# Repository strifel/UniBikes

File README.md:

# UniBikes
Inspired by [traintrackr](https://www.traintrackr.io/) I wanted to create something similar for visualizing bikesharing bikes as my first ever PCB design.

Unibikes shows the 10 bike sharing locations at TU Dortmund University in germany with an RGB LED each.
Each LED can therefore represent if there are none, some or a few bikes at that station.

## Data
The micropython code directly receives the rgb values for each LED from a backend.

## Components
| Component name | Component        |
| -------------- | ---------------- |
| D1 to D10      | WS2812B LED      |
| J0             | USB C Receptable |
| J1 and J2      | 4 Pin header     |
| J3             | 2 Pin header     |
| U1             | ESP32 C3         |
| U2             | TLV1117 3.3V     |
| SW1 to SW3     | Push button      |
| R1             | 1k Resistor      |
| R2 to R4       | 10k Resistor     |
| R5 and R6      | 5.1k Resistor    |
| C1 and C4      | 10uF Capacitor   |
| C2             | 1 uF Capacitor   |
| C3             | 100nF Capacitor  |

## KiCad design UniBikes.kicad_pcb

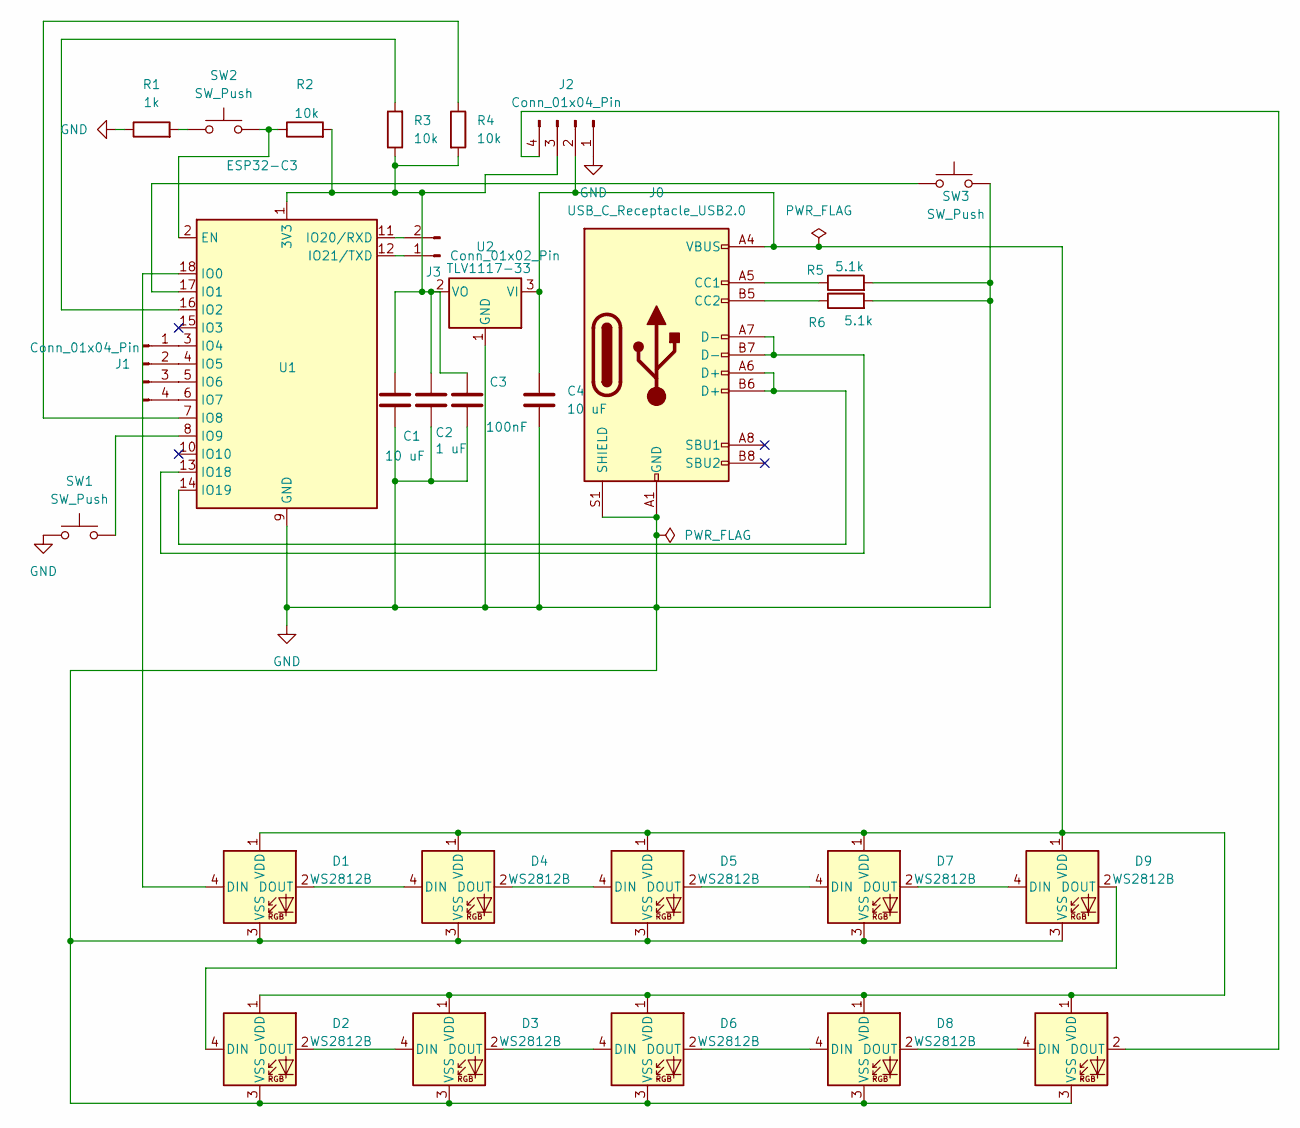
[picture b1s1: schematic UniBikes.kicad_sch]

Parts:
C1, C4: 10 uF; C_0603_1608Metric_Pad1.08x0.95mm_HandSolder
C2: 1 uF; C_0603_1608Metric_Pad1.08x0.95mm_HandSolder
C3: 100nF; C_0603_1608Metric_Pad1.08x0.95mm_HandSolder
D1, D2, D3, D4, D5, D6, D7, D8, D9, D10: WS2812B; LED_WS2812B_PLCC4_5.0x5.0mm_P3.2mm
J0: USB_C_Receptacle_USB2.0; USB_C_Receptacle_GCT_USB4110
J1, J2: Conn_01x04_Pin; PinSocket_1x04_P2.54mm_Vertical_SMD_Pin1Left
J3: Conn_01x02_Pin; PinSocket_1x02_P2.54mm_Vertical_SMD_Pin1Left
R1: 1k; R_0603_1608Metric_Pad0.98x0.95mm_HandSolder
R2, R3, R4: 10k; R_0603_1608Metric_Pad0.98x0.95mm_HandSolder
R5, R6: 5.1k; R_0603_1608Metric_Pad0.98x0.95mm_HandSolder
SW1, SW2, SW3: SW_Push; SW_Push_SPST_NO_Alps_SKRK
U1: ESP32-C3; ESP32-C3-WROOM-02
U2: TLV1117-33; SOT-223-3_TabPin2

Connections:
GND: C1.2, C2.2, C3.2, C4.2, D1.3 (VSS), D2.3 (VSS), D3.3 (VSS), D4.3 (VSS), D5.3 (VSS), D6.3 (VSS), D7.3 (VSS), D8.3 (VSS), D9.3 (VSS), D10.3 (VSS), J0.A1 (GND), J0.A12 (GND), J0.B1 (GND), J0.B12 (GND), J0.S1 (SHIELD), J2.1, R1.1, R5.2, R6.2, SW1.1, SW3.2, U1.9 (GND), U1.19 (GND), U2.1 (GND)
unnamed: D1.4 (DIN), U1.18 (IO0)
unnamed: D1.2 (DOUT), D4.4 (DIN)
unnamed: C4.1, D1.1 (VDD), D2.1 (VDD), D3.1 (VDD), D4.1 (VDD), D5.1 (VDD), D6.1 (VDD), D7.1 (VDD), D8.1 (VDD), D9.1 (VDD), D10.1 (VDD), J0.A4 (VBUS), J0.A9 (VBUS), J0.B4 (VBUS), J0.B9 (VBUS), J2.2, U2.3 (VI)
unnamed: D2.4 (DIN), D9.2 (DOUT)
unnamed: D2.2 (DOUT), D3.4 (DIN)
unnamed: D3.2 (DOUT), D6.4 (DIN)
unnamed: D4.2 (DOUT), D5.4 (DIN)
unnamed: D5.2 (DOUT), D7.4 (DIN)
unnamed: D6.2 (DOUT), D8.4 (DIN)
unnamed: D7.2 (DOUT), D9.4 (DIN)
unnamed: D8.2 (DOUT), D10.4 (DIN)
unnamed: D10.2 (DOUT), J2.4
unnamed: J0.A5 (CC1), R5.1
unnamed: J0.B5 (CC2), R6.1
unnamed: J1.1, U1.3 (IO4)
unnamed: J1.2, U1.4 (IO5)
unnamed: J1.3, U1.5 (IO6)
unnamed: J1.4, U1.6 (IO7)
unnamed: C1.1, C2.1, C3.1, J2.3, R2.2, R3.1, R4.2, U1.1 (3V3), U2.2 (VO)
unnamed: J3.1, U1.12 (IO21/TXD)
unnamed: J3.2, U1.11 (IO20/RXD)
unnamed: R1.2, SW2.1
unnamed: R2.1, SW2.2, U1.2 (EN)
unnamed: SW3.1, U1.17 (IO1)
unnamed: R3.2, U1.16 (IO2)
unnamed: R4.1, U1.7 (IO8)
unnamed: SW1.2, U1.8 (IO9)
unnamed: J0.A7 (D-), J0.B7 (D-), U1.13 (IO18)
unnamed: J0.A6 (D+), J0.B6 (D+), U1.14 (IO19)

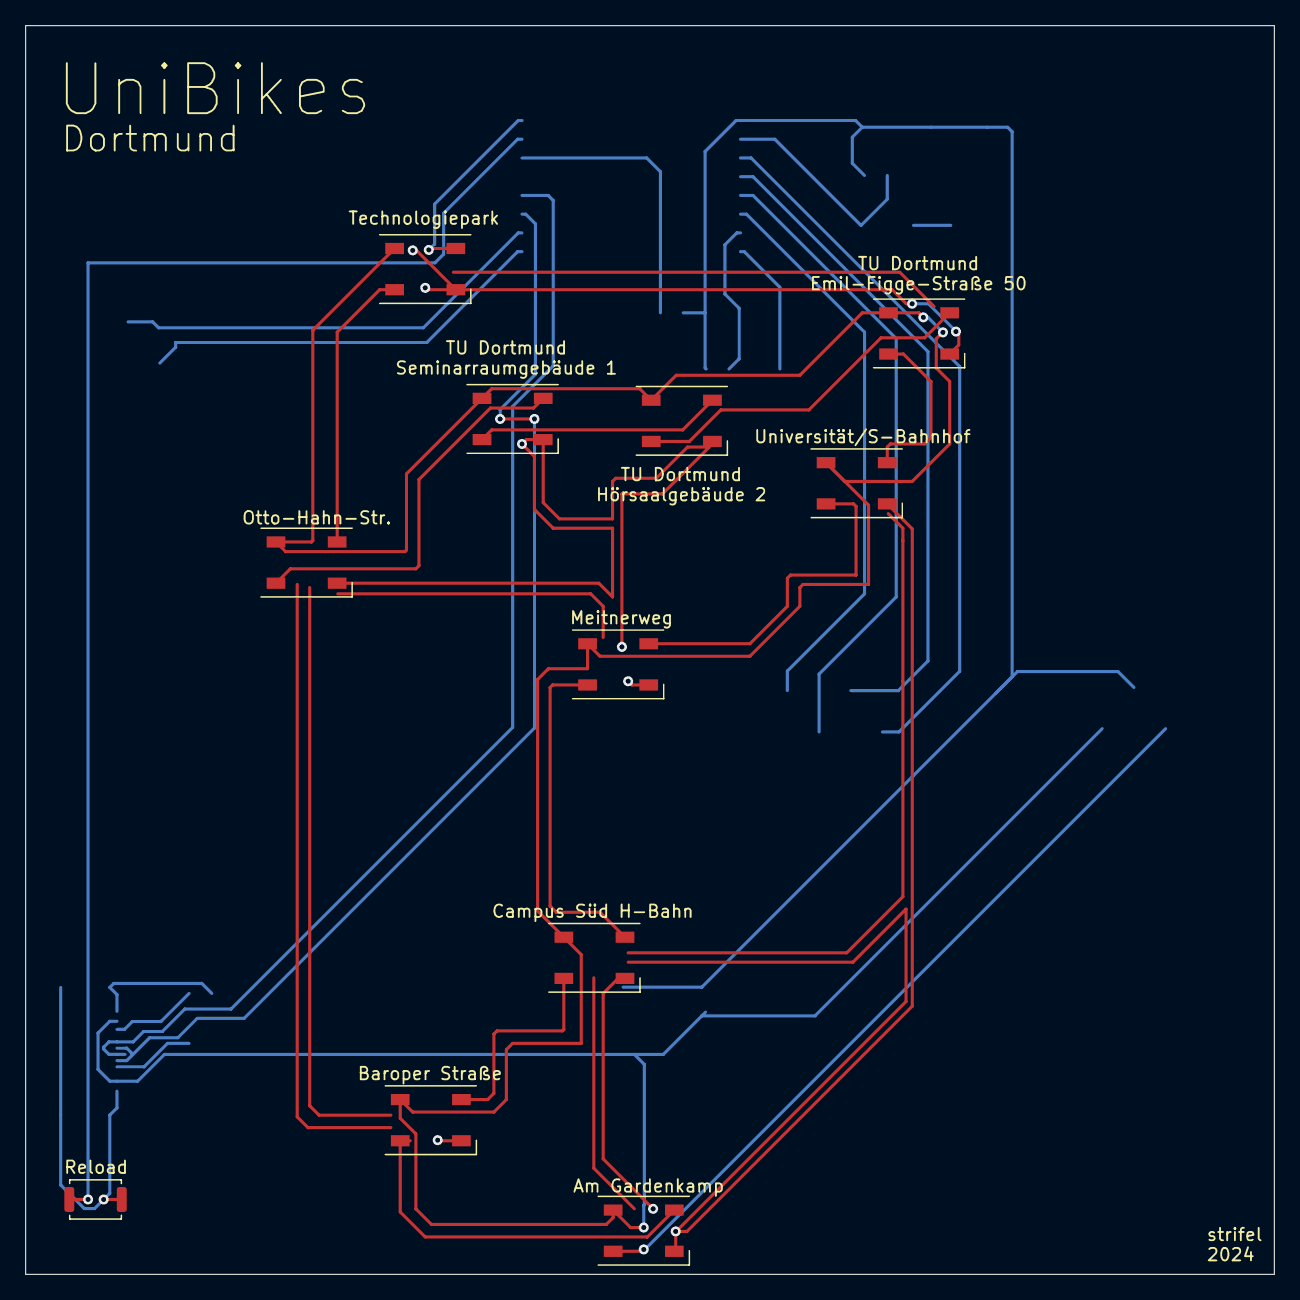
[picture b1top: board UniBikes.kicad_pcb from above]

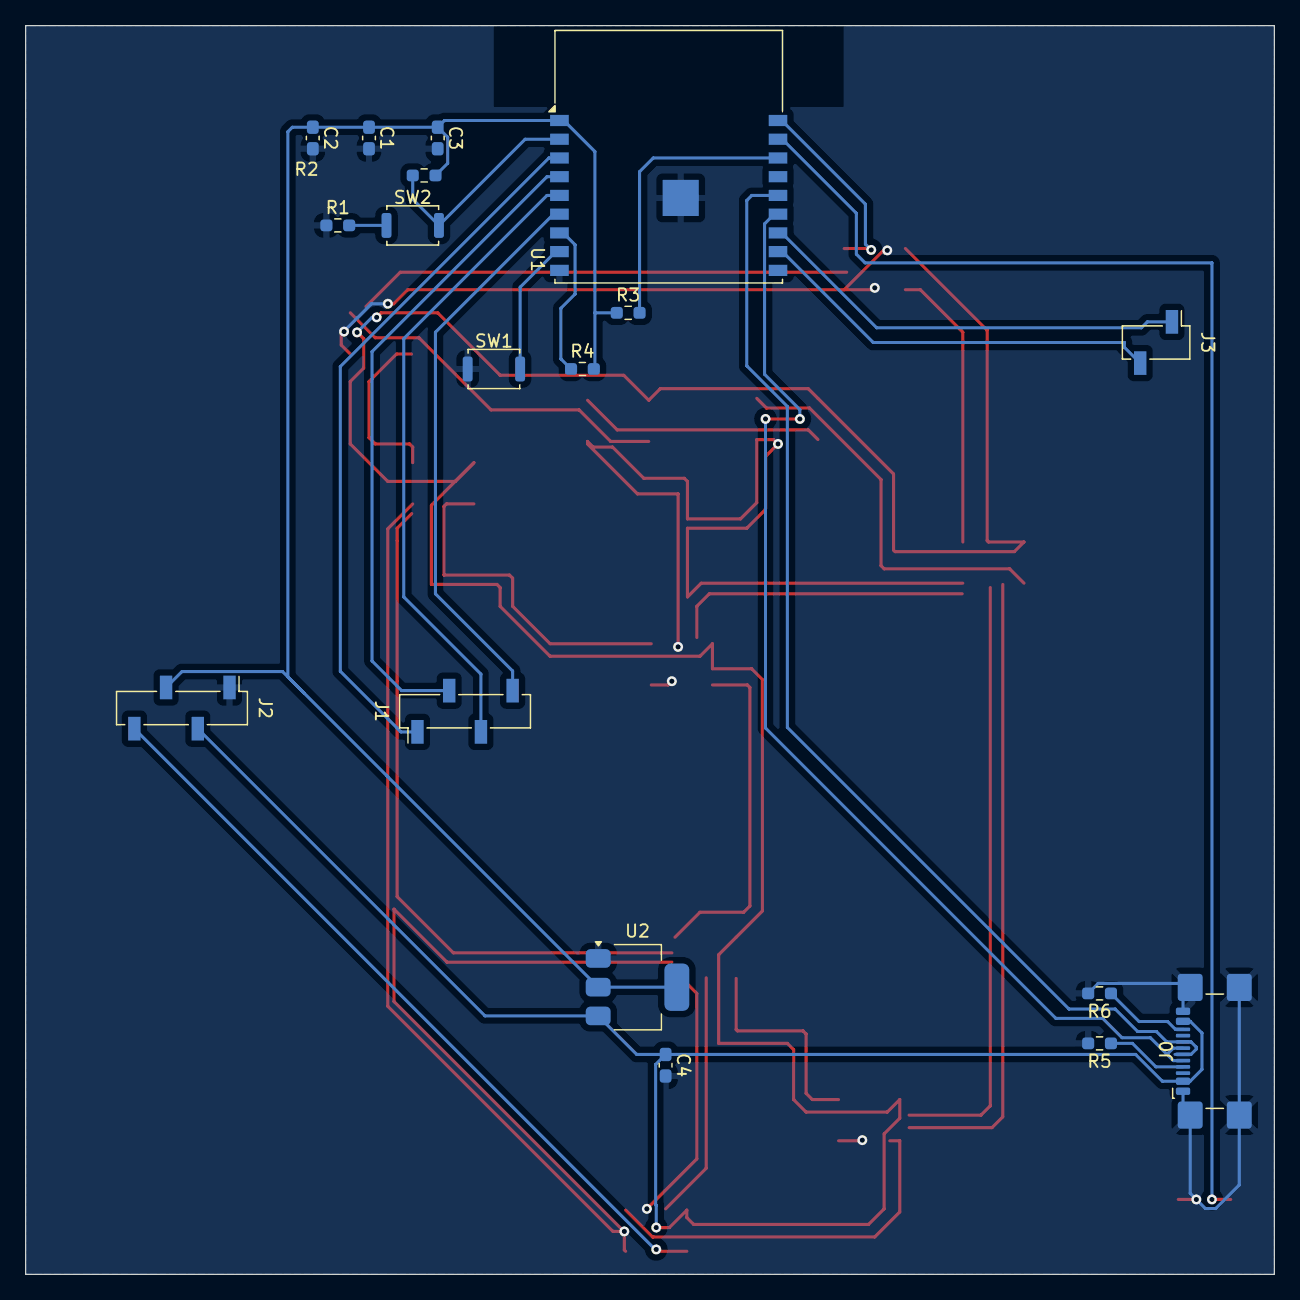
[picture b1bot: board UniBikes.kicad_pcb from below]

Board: 2 copper layers, 100.0 x 100.0 mm, 29 parts (18 on the bottom side), 30 nets.
